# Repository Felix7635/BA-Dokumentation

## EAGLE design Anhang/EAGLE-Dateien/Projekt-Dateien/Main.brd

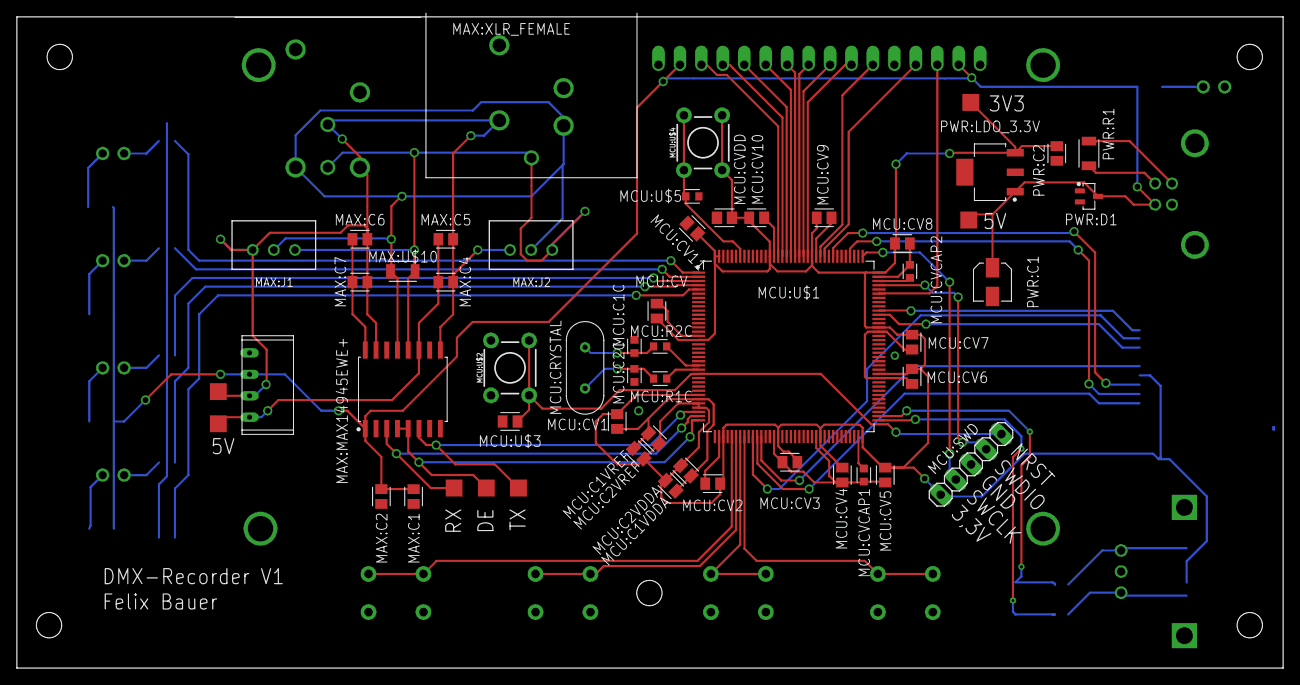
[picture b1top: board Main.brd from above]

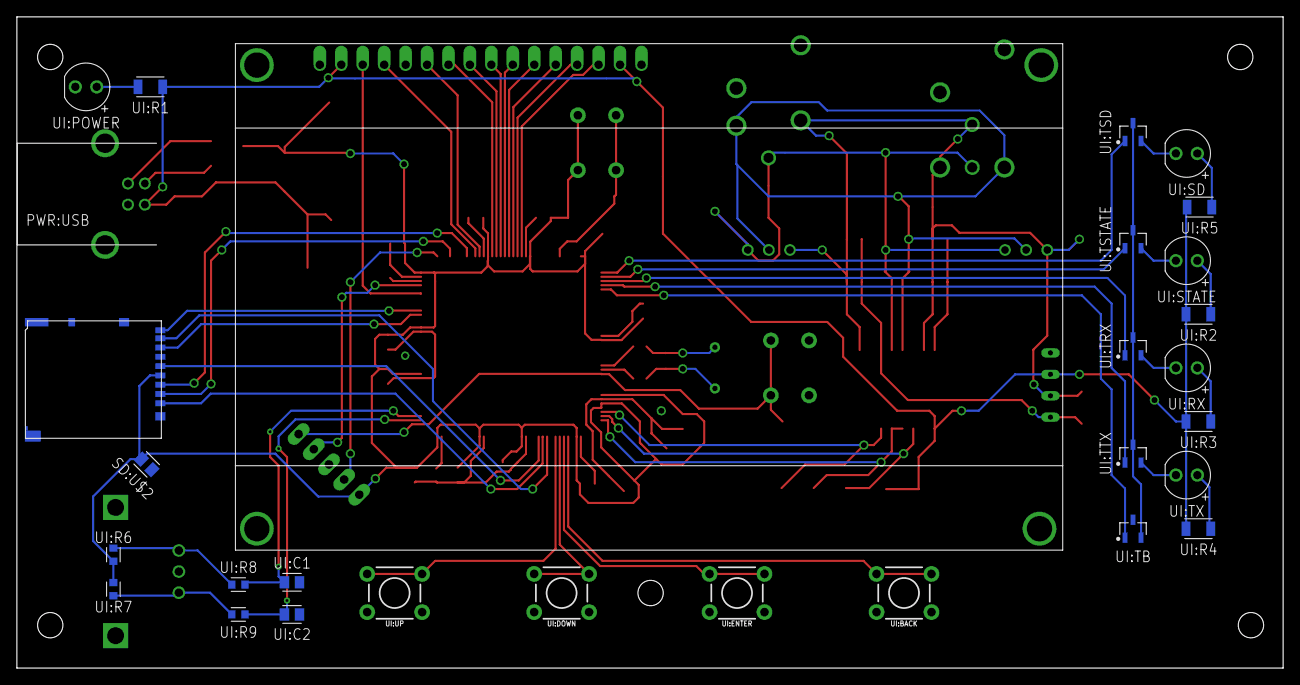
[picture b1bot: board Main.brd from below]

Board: 2 copper layers, 150.0 x 77.1 mm, 85 parts (30 on the bottom side), 64 nets.

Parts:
LCD:U$1: LCD_4X202004A; LCD
MAX:C1, MAX:C5, MAX:C7: 1uF; CAPC2012X100N
MAX:C2, MAX:C4, MAX:C6: 0.1uF; CAPC2012X90N
MAX:DC/DC: CONVERTER_5V/5V_DCTRACO; 5V/5V_DC_CONVERTER_TRACO
MAX:J1, MAX:J2: 3A/250V; B3B-XH-A
MAX:MAX14945EWE+: DRIVER_MAX14945EWE+; SOIC127P1032X265-16N
MAX:U$2, MAX:U$3, MAX:U$4, MAX:U$5, MAX:U$6: MESSPUNKT
MAX:U$10: 120; RESC3115X56N
MAX:XLR_FEMALE: CONNECTOR_XLR_FEMALE_NC3FAAH-0; NC3FAAH-0
MAX:XLR_MALE: CONNECTOR_XLR_MALE_NC3MBH-B; NC3MBH-B
MCU:C1C, MCU:C2C: 26pF; CAPC1608X97N
MCU:C1VDDA, MCU:C1VREF: 1uF; CAPC2012X100N
MCU:C2VDDA, MCU:C2VREF: 0.1uF; CAPC2012X90N
MCU:CRYSTAL: 25MHz; XTALRR488W43L1077T434H350B
MCU:CV, MCU:CV1, MCU:CV2, MCU:CV3, MCU:CV4, MCU:CV5, MCU:CV6, MCU:CV7, MCU:CV8, MCU:CV9, MCU:CV10, MCU:CV11: 0.1uF; CAPC2012X90N
MCU:CVCAP1, MCU:CVCAP2: 2,2uF; CAPC1608X90N
MCU:CVDD: 4,7uF; CAPC2012X140N
MCU:R1C: 1k2; RESC1608X55N
MCU:R2C: 0; RESC1608X55N
MCU:SWD: PINHD-1X5; 1X05
MCU:U$1: STM32F446ZELQFP144; QFP50P2200X2200X160-144N
MCU:U$2, MCU:U$4: BUTTON_6MM; TACTILE_SWITCH_PTH_6.0MM
MCU:U$3: 0.1uF; CAPC2012X90N
MCU:U$5: 10k; RESC1608X55N
PWR:C1: 10uF; CAPAE430X610N
PWR:C2: 1uF; CAPC2012X100N
PWR:D1: ZDIODEBZX84C6V2LT1G; SOT65P237X111-3N
PWR:LDO_3.3V: LDO_TC1262-3.3VDB; SOT230P700X180-4N
PWR:R1: 120; RESC3115X56N
PWR:U$5, PWR:U$6: MESSPUNKT
PWR:USB: CONNECTOR_USB-TYPE_B61400416121; USB-TYPE_B_CONNECTOR
SD:U$1: CONNECTOR_DM3AT-SF-PEJM5; DM3AT-SF-PEJM5
SD:U$2: 0.1uF; CAPC2012X90N
UI:BACK: BUTTON_6MM; TACTILE_SWITCH_PTH_6.0MM
UI:C1, UI:C2: 10nF; CAPC2012X145N
UI:DOWN: BUTTON_6MM; TACTILE_SWITCH_PTH_6.0MM
UI:ENCODER: ENCODER; EC12E2420404
UI:ENTER: BUTTON_6MM; TACTILE_SWITCH_PTH_6.0MM
UI:POWER: LEDBLUE; LED_5MM_BLUE
UI:R1, UI:R2, UI:R3, UI:R4, UI:R5: 120; RESC3115X56N
UI:R6, UI:R7, UI:R8, UI:R9: 10k; RESC1608X55N
UI:RX: LEDYELLOW; LED_5MM_YELLOW
UI:SD: LEDGREEN; LED_5MM_GREEN
UI:STATE: LEDRED; LED_5MM_RED
UI:TB: TRANSISTOR_NPNMMBTH10LT3G; SOT95P237X111-3N
UI:TRX: TRANSISTOR_NPNMMBTH10LT3G; SOT95P237X111-3N
UI:TSD: TRANSISTOR_NPNMMBTH10LT3G; SOT95P237X111-3N
UI:TSTATE: TRANSISTOR_NPNMMBTH10LT3G; SOT95P237X111-3N
UI:TTX: TRANSISTOR_NPNMMBTH10LT3G; SOT95P237X111-3N
UI:TX: LEDBLUE; LED_5MM_BLUE
UI:UP: BUTTON_6MM; TACTILE_SWITCH_PTH_6.0MM

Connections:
3,3V: MCU:C1VDDA.1, MCU:C1VREF.1, MCU:C2VDDA.1, MCU:C2VREF.1, MCU:CV.1, MCU:CV1.1, MCU:CV2.1, MCU:CV3.1, MCU:CV4.1, MCU:CV5.1, MCU:CV6.1, MCU:CV7.1, MCU:CV8.1, MCU:CV9.1, MCU:CV10.1, MCU:CV11.1, MCU:CVDD.1, MCU:SWD.1, MCU:U$1.17, MCU:U$1.30, MCU:U$1.32, MCU:U$1.33, MCU:U$1.39, MCU:U$1.52, MCU:U$1.62, MCU:U$1.72, MCU:U$1.84, MCU:U$1.95, MCU:U$1.108, MCU:U$1.121, MCU:U$1.131, MCU:U$1.143, MCU:U$1.144, MCU:U$4.3, MCU:U$4.4, PWR:C2.1, PWR:LDO_3.3V.VOUT, PWR:U$6.P$1, SD:U$1.VDD, SD:U$2.1, UI:R6.1, UI:R7.1
+5V: LCD:U$1.A, LCD:U$1.VDD, MAX:C1.1, MAX:C2.1, MAX:DC/DC.+VIN, MAX:MAX14945EWE+.1, PWR:C1.1, PWR:D1.3, PWR:LDO_3.3V.VIN, PWR:U$5.P$1, PWR:USB.VCC, UI:R1.1, UI:R2.1, UI:R3.1, UI:R4.1, UI:R5.1
GND: LCD:U$1.K, LCD:U$1.RW, LCD:U$1.VSS, MAX:C1.2, MAX:C2.2, MAX:DC/DC.-VIN, MAX:MAX14945EWE+.2, MAX:MAX14945EWE+.8, MCU:C1C.1, MCU:C1VDDA.2, MCU:C1VREF.2, MCU:C2C.2, MCU:C2VDDA.2, MCU:C2VREF.2, MCU:CV.2, MCU:CV1.2, MCU:CV2.2, MCU:CV3.2, MCU:CV4.2, MCU:CV5.2, MCU:CV6.2, MCU:CV7.2, MCU:CV8.2, MCU:CV9.2, MCU:CV10.2, MCU:CV11.2, MCU:CVCAP1.2, MCU:CVCAP2.2, MCU:CVDD.2, MCU:SWD.3, MCU:U$1.16, MCU:U$1.31, MCU:U$1.38, MCU:U$1.51, MCU:U$1.61, MCU:U$1.83, MCU:U$1.94, MCU:U$1.107, MCU:U$1.120, MCU:U$1.130, MCU:U$2.1, MCU:U$2.2, MCU:U$3.2, MCU:U$5.2, PWR:C1.2, PWR:C2.2, PWR:D1.1, PWR:LDO_3.3V.GND1, PWR:LDO_3.3V.GND2, PWR:USB.GND, SD:U$1.CARD_DETECTION_SWIT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, SD:U$1.VSS, SD:U$2.2, UI:BACK.1, UI:BACK.2, UI:C1.2, UI:C2.2, UI:DOWN.1, UI:DOWN.2, UI:ENCODER.C, UI:ENTER.1, UI:ENTER.2, UI:POWER.2, UI:TB.3, UI:UP.1, UI:UP.2
MAX:GNDB: MAX:C4.2, MAX:C5.2, MAX:C6.2, MAX:C7.2, MAX:DC/DC.-VOUT, MAX:J1.1, MAX:J2.1, MAX:MAX14945EWE+.9, MAX:MAX14945EWE+.15, MAX:U$2.P$1, MAX:XLR_FEMALE.1, MAX:XLR_MALE.1, MAX:XLR_MALE.G
MAX:N$1: MAX:J1.3, MAX:J2.3, MAX:MAX14945EWE+.12, MAX:U$10.1, MAX:XLR_FEMALE.3, MAX:XLR_MALE.3
MAX:N$2: MAX:J1.2, MAX:J2.2, MAX:MAX14945EWE+.13, MAX:U$10.2, MAX:XLR_FEMALE.2, MAX:XLR_MALE.2
MAX:VDDB: MAX:C6.1, MAX:C7.1, MAX:MAX14945EWE+.16
MAX:VLDO: MAX:C4.1, MAX:C5.1, MAX:DC/DC.+VOUT, MAX:MAX14945EWE+.11, MAX:U$3.P$1
MCU:BOOT0: MCU:U$1.138, MCU:U$4.1, MCU:U$4.2, MCU:U$5.1
MCU:N$2: MCU:C1C.2, MCU:CRYSTAL.1, MCU:R2C.1
MCU:N$6: MCU:C2C.1, MCU:CRYSTAL.2, MCU:R1C.1
MCU:NRST: MCU:SWD.5, MCU:U$1.25, MCU:U$2.3, MCU:U$2.4, MCU:U$3.1
MCU:OSC_IN: MCU:R2C.2, MCU:U$1.23
MCU:OSC_OUT: MCU:R1C.2, MCU:U$1.24
MCU:SWCLK: MCU:SWD.2, MCU:U$1.109
MCU:SWDIO: MCU:SWD.4, MCU:U$1.105
MCU:VCAP1: MCU:CVCAP1.1, MCU:U$1.71
MCU:VCAP2: MCU:CVCAP2.1, MCU:U$1.106
unnamed: MCU:U$1.116, SD:U$1.CMD
unnamed: MCU:U$1.48, SD:U$1.CLK
unnamed: MCU:U$1.112, SD:U$1.CD/DAT3
unnamed: MAX:MAX14945EWE+.3, MAX:U$6.P$1, MCU:U$1.35
unnamed: MAX:MAX14945EWE+.6, MAX:U$4.P$1, MCU:U$1.34
unnamed: MCU:U$1.47, SD:U$1.DAT2
unnamed: MCU:U$1.46, SD:U$1.DAT1
unnamed: MCU:U$1.98, SD:U$1.DAT0
unnamed: LCD:U$1.V0, MCU:U$1.103
unnamed: MCU:U$1.74, UI:C1.1, UI:R8.1
unnamed: LCD:U$1.E, MCU:U$1.119
unnamed: LCD:U$1.RS, MCU:U$1.118
unnamed: LCD:U$1.D0, MCU:U$1.122
unnamed: LCD:U$1.D1, MCU:U$1.123
unnamed: LCD:U$1.D4, MCU:U$1.126
unnamed: LCD:U$1.D5, MCU:U$1.127
unnamed: LCD:U$1.D6, MCU:U$1.128
unnamed: LCD:U$1.D7, MCU:U$1.129
unnamed: LCD:U$1.D2, MCU:U$1.124
unnamed: LCD:U$1.D3, MCU:U$1.125
unnamed: MCU:U$1.73, UI:C2.1, UI:R9.2
unnamed: MCU:U$1.41, UI:BACK.3, UI:BACK.4
unnamed: MCU:U$1.42, UI:ENTER.3, UI:ENTER.4
unnamed: MCU:U$1.43, UI:DOWN.3, UI:DOWN.4
unnamed: MCU:U$1.44, UI:UP.3, UI:UP.4
unnamed: MAX:MAX14945EWE+.4, MAX:MAX14945EWE+.5, MAX:U$5.P$1, MCU:U$1.36
unnamed: MCU:U$1.2, UI:TSTATE.1
unnamed: MCU:U$1.5, UI:TB.1
unnamed: MCU:U$1.4, UI:TTX.1
unnamed: MCU:U$1.3, UI:TRX.1
unnamed: MCU:U$1.1, UI:TSD.1
unnamed: MCU:U$1.99, SD:U$1.CARD_DETECTION_SWIT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
PWR:D+: PWR:R1.1, PWR:USB.D+
PWR:D-: PWR:R1.2, PWR:USB.D-
UI:N$1: UI:POWER.1, UI:R1.2
UI:N$2: UI:R2.2, UI:STATE.1
UI:N$3: UI:R3.2, UI:RX.1
UI:N$4: UI:R4.2, UI:TX.1
UI:N$7: UI:R5.2, UI:SD.1
UI:N$8: UI:TB.2, UI:TRX.3, UI:TSD.3, UI:TSTATE.3, UI:TTX.3
UI:N$9: UI:STATE.2, UI:TSTATE.2
UI:N$10: UI:RX.2, UI:TRX.2
UI:N$11: UI:TTX.2, UI:TX.2
UI:N$12: UI:SD.2, UI:TSD.2
UI:N$13: UI:ENCODER.B, UI:R6.2, UI:R8.2
UI:N$14: UI:ENCODER.A, UI:R7.2, UI:R9.1

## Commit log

2021-06-16 Inhaltsverzeichnis.tex hinzugefügt
2021-06-16 Titelblatt.tex hinzugefügt
2021-06-16 Titelblatt und Inhaltsverzeichnis hinzugefügt
2021-06-17 Titelblatt fertiggestellt
2021-06-17 Literaturbibliothek hinzugefügt
2021-06-17 Layout angepasst und packages hinzugefügt
2021-06-17 Abbildungsverzeichnis hinzugefügt deutsches Sprachpaket aktiviert
2021-06-17 Selbstständigkeitserklärung und Sperrvermerk hinzugefügt
2021-06-21 Einträge zum Inhaltsverzeichnis hinzugefügt
    Außerdem Code-Einbettung ermöglicht durch listings package
2021-06-22 Konzept zum Inhaltsverzeichnis hinzugefügt
2021-06-28 Schaltungsprinzip 1. Entwurf
2021-06-28 Konzept mit Gegenstand und Ziel ersetzt
2021-08-06 Ersetzt mit GegenstandundZiel.tex
2021-08-06 Datenblätter der wichtigen Komponenten hinzugefügt
2021-08-06 Bilder hinzugefügt
2021-08-06 Abbildungsverzeichnis hinzugefügt
2021-08-06 Upload aktueller Version
2021-08-06 Hardware Dateien in Hardware Ordner verschoben
2021-08-11 Kapitel Taster hinzugefügt
2021-08-12 Rechtschreibfehler korrigiert
2021-08-12 Kapitel Software hinzugefügt
2021-08-15 Fehler korrigiert
2021-08-15 Kapitel DMX Aufnahme und Wiedergabe hinzugefügt
    Kapitel Wiedergabe nahezu fertig
    Kapitel Aufnahme: Bisher nur Codeausschnitte eingefügt und etwas Text
2021-08-17 Kapitel Aufnahme eines DMX-Datenpaketes fertiggestellt
2021-08-25 Kapitel CubeMX hinzugefügt
2021-08-25 Codeausschnittsverzeichnis hinzugefügt
2021-08-25 Kapitel SD hinzugefügt
2021-08-25 Fehler im lstlisting behoben
2021-08-25 Kleine Fehler behoben
2021-08-25 Neue Quellen hinzugefügt
2021-08-25 Kapitel CubeIDE hinzugefügt
2021-08-25 .lol-Dateien zu .gitignore hinzugefügt
2021-08-25 Literatur hinzugefügt
2021-08-25 Kapitel HAL hinzugefügt
2021-08-27 Label für Kapitel hinzugefügt
2021-08-27 Abbildungen hinzugefügt
    Abbildungen für die Kapitel Einstellungen und Menü
2021-08-27 Kapitel LCD fertiggestellt
2021-08-27 Kapitel Menu erstellt und fertiggestellt
2021-08-27 Kapitel Einstellungen erstellt und Bearbeitung begonnen
2021-08-27 Input für die Dateien Menü und Einstellungen hinzugefügt
2021-08-27 Kleine, nicht wesentliche Änderungen
2021-08-27 Aktuelle Version
2021-08-31 Kapitel Aufnahmefunktion fertiggestellt
2021-08-31 Caption-Text bearbeitet
2021-08-31 Flussdiagramm der Wiedergabefunktion zum Anhang hinzugefügt
2021-08-31 FLussdiagramm der Aufnahmefunktion hinzugefügt
2021-08-31 Fehlende Bedingung ergänzt
2021-08-31 Kapitel zu subsubsection geändert
2021-08-31 Kapitel Aufnahme löschen hinzugefügt
2021-08-31 Kapitel Wiedergabefunktion hinzugefügt
2021-09-02 Datei für Abkürzungsverzeichnis hinzugefügt & Tabellenoptik angepasst
2021-09-02 Umformuliert
2021-09-02 Text zu Hauptkapitel hinzugefügt
2021-09-02 Kapitel DMX-Struktur hinzugefügt und Text zu Hauptkapitel hinzugefügt
2021-09-02 Kapitel Wiedergabefunktion fertiggestellt
2021-09-02 Formulierungen verbessert
2021-09-02 Flussdiagramm für Standard-Wiedergabe hinzugefügt
2021-09-03 Label hinzugefügt
2021-09-03 Zusammenfassung fertiggestellt
2021-09-03 Abkürzungsverzeichnis hinzugefügt
2021-09-08 Resultatfotos hinzugefügt
2021-09-08 Tabellenbeschriftung über die Tabelle gesetzt
2021-09-08 Nicht dargestellte Unterstriche hinzugefügt
2021-09-10 Dateien zum Anhang hinzugefügt
2021-09-12 Dateien zum CD-Anhang hinzugefügt
2021-09-12 Abbildungsverzeichnis auf neue Seite verschoben
2021-09-12 XLR Abkürzung entfernt
2021-09-12 Verzeichnis auf neue Seite verschoben
2021-09-12 Einleitung hinzugefügt
2021-09-12 Korrekturen eingefügt
2021-09-13 Eintrag zum Inhaltsverzeichnis hnzugefügt
2021-09-13 Anhang fertiggestellt
2021-09-13 Aufgeräumt
2021-09-13 Eintrag zum Inhaltsverzeichnis hinzugefügt
2021-09-13 Danksagung hinzugefügt
2021-09-13 Gender disclaimer hinzugefügt
2021-09-13 Freigestellte Bilder hinzugefügt
2021-09-13 Markierung überarbeitet
2021-09-13 Korrekturen eingepflegt
2021-09-13 DOIs und Links zu den Quellen hinzugefügt
